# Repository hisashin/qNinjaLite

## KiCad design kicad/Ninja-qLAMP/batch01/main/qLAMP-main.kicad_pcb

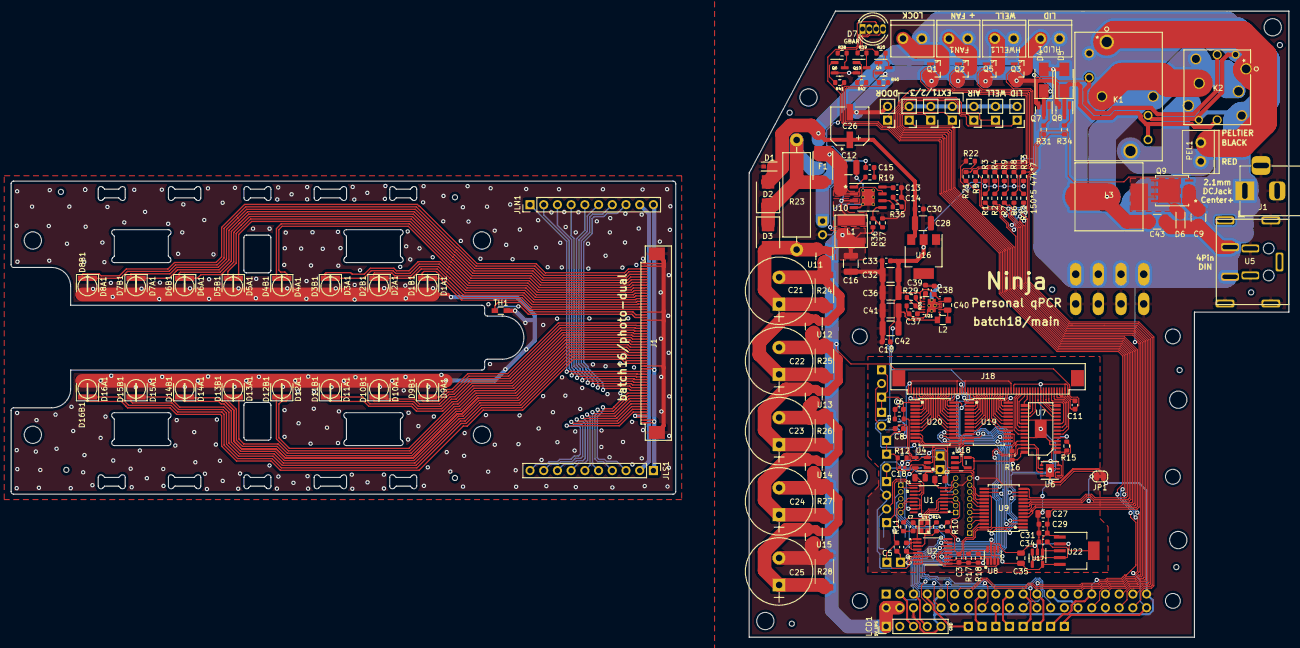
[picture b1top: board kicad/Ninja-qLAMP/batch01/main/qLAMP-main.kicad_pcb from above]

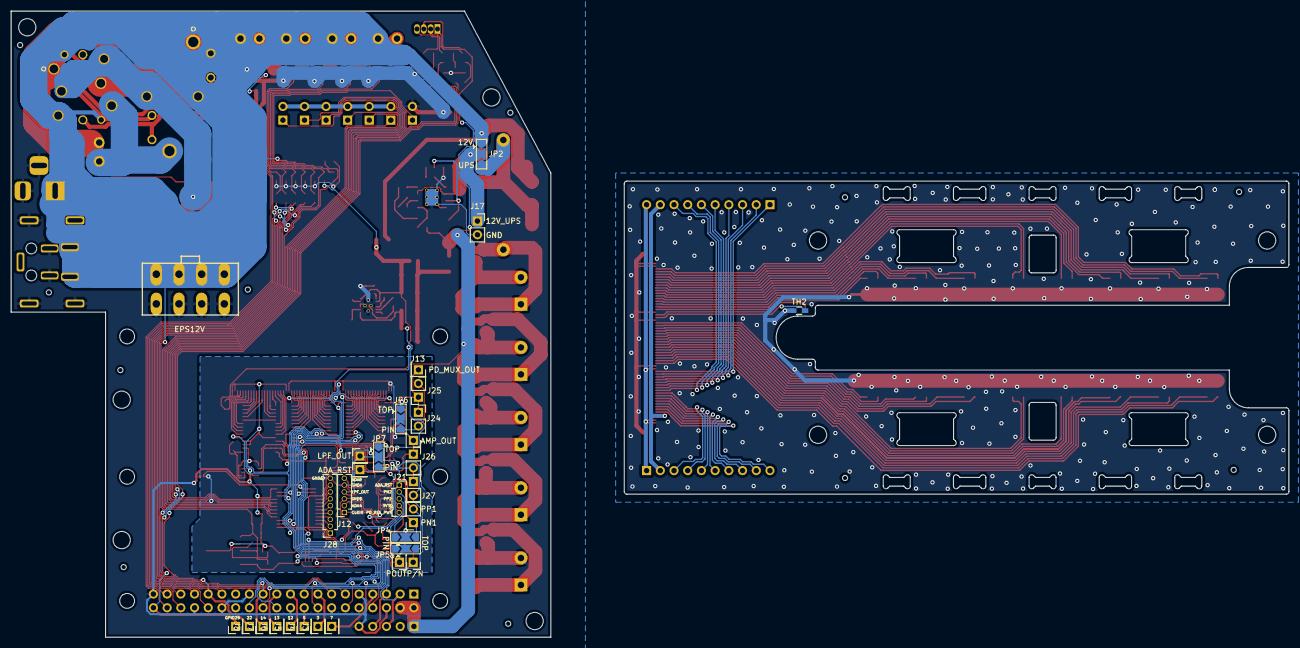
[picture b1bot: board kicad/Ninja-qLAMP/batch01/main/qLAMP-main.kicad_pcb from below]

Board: 2 copper layers, 100.0 x 116.0 mm, 210 parts (30 on the bottom side), 170 nets.

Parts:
C1, C2, C27, C35: 4.7uF; C_0805_2012Metric
C3, C4, C5, C7, C8, C10, C11, C13, C29, C30, C33: 0.1uF; C_0603_1608Metric
C6: DNP(<1pF); C_0603_1608Metric
C9, C12, C16, C28, C32, C36, C41, C42, C43: 22uF; C_1210_3225Metric
C14, C15, C31: 0.01uF; C_0603_1608Metric
C18: 330pF; C_0402_1005Metric
C21, C22, C23, C24, C25: 10F2.7V; CP_Radial_D12.5mm_P5.00mm
C26: 100uF; 35TZV100M6.3X8
C34: 100pF; C_0603_1608Metric
C37, C38, C39: 1uF; C_0603_1608Metric
C40: 10uF; C_0805_2012Metric
D1, D6: D_Schottky; MSS1P3L-M3&slash_89A
D1A1, D1B1, D2A1, D2B1, D3A1, D3B1, D4A1, D4B1, D5A1, D5B1, D6A1, D6B1, D7A1, D7B1, D8A1, D8B1, D9A1, D9B1, D10A1, D10B1, D11A1, D11B1, D12A1, D12B1, D13A1, D13B1, D14A1, D14B1, D15A1, D15B1, D16A1, D16B1: D_Photo; D_1206
D2, D3: D; D_SMB
D4, D5: DIODE; D_SMA
D7: LED_GBAR; LED_D5.0mm-4_RGB
F1: Fuse; R_2512
FAN1: Screw_Terminal_01x02; TB_SeeedOPL_320110028
HLID1: Screw_Terminal_01x02; TB_SeeedOPL_320110028
HWELL1: Screw_Terminal_01x02; TB_SeeedOPL_320110028
J1: Barrel_Jack_Switch; BarrelJack_Horizontal
J1#2, J18: Conn_01x60_Male; FFC_60_Ali_HUISHUNFA
J2: Raspberry_Pi_3A_Plus_wpi; Raspberry_Pi_3A+_3B+_4B_Zero_FaceDown_HDMI-R-NOSILK
J3, J4, J5, J6, J7, J8, J9, J11, J20, J23: Conn_01x01_Male; PinHeader_1x01_P2.54mm_Vertical
J12: Conn_01x06_Male; PinSocket_1x06_P1.27mm_Vertical
J13, J14, J15, J16: Conn_01x01_Male; PinSocket_1x01_P2.54mm_Vertical
J17, J22, J24, J25, J26, J27: Conn_01x02_Male; PinSocket_1x02_P2.54mm_Vertical
J19: Conn_01x08_Male; ATX8
J21: Conn_01x05_Male; PinSocket_1x05_P1.27mm_Vertical
J28: Conn_01x09_Male; PinSocket_1x09_P1.27mm_Vertical
JLN1: Conn_01x10_Male; Pin_Header_Straight_1x10_Pitch2.54mm
JLS1: Conn_01x10_Male; Pin_Header_Straight_1x10_Pitch2.54mm
JP1: SolderJumper_2_Bridged; SolderJumper-2_P1.3mm_Bridged_RoundedPad1.0x1.5mm
JP2, JP4, JP5, JP6, JP7: Jumper_3_Open; SolderJumper-3_P2.0mm_Open_TrianglePad1.0x1.5mm
K1: EP2-3L3SAb
K2: EX2-2U1S
L1: 10uH; VLS6045EX-3R3N
L2: 2.2uH; C_0805
L3: SRP1265C-220M; SRP1265C
LCD1: RPI_LCD_TOUCH_7INCH; PinHeader_1x05_P2.54mm_Vertical
LOCK1: Conn_01x02_Male; TB_SeeedOPL_320110028
PEL1: Screw_Terminal_01x02; TB_SeeedOPL_320110028
Q1, Q2, Q3, Q5: Q_NMOS_GSD; SOT95P240X112-3N
Q4, Q6, Q7, Q8, Q10: Q_NPN_BCE; SOT-23
Q9: SIRA88BDP-T1-GE3; PowerPAK_SO-8_Long
R1, R2, R6, R7, R19, R32: 150; R_0603_1608Metric
R3, R4, R5, R8, R9, R16, R21, R33, R36: 47k; R_0603_1608Metric
R10, R11, R12, R14, R22, R31, R34, R35, R37, R40, R41, R42: 10k; R_0603_1608Metric
R13: 10M; R_0603_1608Metric
R15: 180; R_0603_1608Metric
R17: 10k_HP; R_0603_1608Metric
R18: 47k_HP; R_0603_1608Metric
R20, R38, R39: ?; R_0603_1608Metric
R23: 8.2Ω 3W; R_Axial_DIN0516_L15.5mm_D5.0mm_P20.32mm_Horizontal
R24, R25, R26, R27, R28: 1k2W; R_2512_6332Metric
R29: 39k; R_0603_1608Metric
R30: 150k; R_0603_1608Metric
SW1: SW_Reed; PinHeader_1x02_P2.54mm_Vertical
TAIR1: Conn_01x02_Male; PinHeader_1x02_P2.54mm_Vertical
TEXT1, TEXT2, TEXT3: Conn_01x02_Male; PinHeader_1x02_P2.54mm_Vertical
TH1, TH2: Thermistor; R_0603_HandSoldering
TLID1: Conn_01x02_Male; PinHeader_1x02_P2.54mm_Vertical
TWELL1: Conn_01x02_Male; PinHeader_1x02_P2.54mm_Vertical
U1: ADA2200ARUZ
U2: ADS1219IPWR; ADS122C04IPWR
U3: COM1305-0.032768-EXT-T-TR; ASDK-32.768KHZ-LRT
U4: LMP7717MF_NOPB; SOT-23-5
U5: DIN4_PWR; DN4_PWR
U6: MCP4551T-502E/MS; MCP4551T-104E&slash_MF
U7: PCA9955B
U8: TS12A12511DCNR; SOT-23-8
U9, U19, U20: CD74HC4067M96; SSOP-24_5.3x8.2mm_P0.65mm
U10: BD9329AEFJ-E2; HSOP-8-1EP_3.9x4.9mm_P1.27mm_EP2.41x3.1mm_ThermalVias
U11, U12, U13, U14, U15: TL431DBZ; SOT-23
U16: CJT1117-3.3; SOT-223
U17: MCP1755T-3302E/OT; SOT-23-5
U18: SN74LVC1GU04DCKR; SN74LVC1GU04DBVR
U21: TPS63710DRRR
U22: MCP1755T-3302E/DC; SOT-223-6

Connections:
3V3A: C3.1, C35.1, R17.1, R18.1, U2.9 (REFP), U2.12 (AVDD), U17.5 (VOUT), U22.5 (VOUT)
3V3D: C3.2, C7.1, C10.1, C32.1, C33.1, C36.1, C38.1, J21.4, R5.1, R10.2, R11.2, R14.2, R16.2, U1.12 (VDD), U1.14 (SDIO/SDA), U1.15 (SCLK/SCL), U2.3 (RESET_N), U2.13 (DVDD), U3.4 (3V3), U4.5 (V+), U6.1 (HVC/A0), U6.5 (P0A), U6.8 (VDD), U7.2 (AD0), U7.28 (VDD), U8.4 (V+), U9.15 (*E), U9.24 (VCC), U16.2 (OUTPUT), U18.5, U19.24 (VCC), U20.24 (VCC), U21.2 (EN), U21.12 (VIN)
5V_UPS: C11.1, C16.2, D7.3 (A), J2.2 (5V), J2.4 (5V), J18.3, J18.4, L1.1, LCD1.1 (5V), R36.1
12V: C9.1, C26.1, C27.1, C28.1, C29.1, C30.1, C31.1, C43.1, D1.1 (K), D2.2 (A), D4.2 (A), D5.2 (A), D6.1 (K), FAN1.1, HLID1.1, HWELL1.1, J1.1, J19.5, J19.6, J19.7, J19.8, JP2.1 (A), K1.2, K1.4, K1.6, K2.2, K2.5, K2.7, K2.9, LOCK1.1, R21.1, U5.1 (VIN1), U5.2 (VIN2), U16.3 (INPUT), U17.1 (VIN), U17.3 (SHDN), U22.1 (VIN), U22.3 (SHDN)
12V_UPS: C12.2, F1.1, J17.1, JP2.2 (C), U10.2 (IN), U10.7 (EN)
-1V: C41.1, C42.1, L2.2, U4.2 (V-), U18.3, U19.12 (GND), U20.12 (GND), U21.7 (VOUT)
/3V3/PWRGD: C34.1, U17.4 (PWRGD), U22.4 (PWRGD)
/5V_UPS/5V_SW: C15.2, L1.2, U10.3 (SW)
/FAN: J2.29 (GPIO21), R2.2
/GPIO3: J2.15 (GPIO3), J3.1
/GPIO5: J2.18 (GPIO5), J4.1
/GPIO7: J2.7 (GPIO7), J11.1
/GPIO12: J2.19 (GPIO12/MOSI), J5.1
/GPIO13: J2.21 (GPIO13/MISO), J6.1
/GPIO14: J2.23 (GPIO14/SCLK), J7.1, R40.2
/GPIO22: J2.31 (GPIO22), J8.1, R41.2
/GPIO29: J2.40 (GPIO29), J9.1, R42.2
/LID_HEATER: J2.13 (GPIO2), R6.2
/Photo/ADA4: J12.2, R11.1, U1.4 (*BOOT)
/Photo/ADA8: C2.1, J12.6, U1.8 (VOCM)
/Photo/ADA_RST: C1.1, J20.1, J21.1, R10.1, U1.9 (*RST)
/Photo/AMP_OUT: C8.1, J16.1, J26.1, JP6.2 (C), R12.2, U4.1 (OUT)
/Photo/LPF_OUT: J12.4, J23.1, JP7.2 (C), U1.6 (INP)
/Photo/PHOTO_OUT_N: C5.1, J14.1, JP4.2 (C), U2.7 (AIN2)
/Photo/PHOTO_OUT_P: C5.2, J15.1, JP5.2 (C), U2.6 (AIN3)
/Photo/PN1: J22.1, JP4.3 (B), U1.10 (OUTN)
/Photo/PN2: J21.2, JP4.1 (A)
/Photo/PP1: J22.2, JP5.3 (B), U1.11 (OUTP)
/Photo/PP2: J21.3, JP5.1 (A)
/PhotoLED/LED_IREF: R15.2, U6.6 (P0W)
/PhotoMUX/MUX_SELECT_INV: U18.4, U19.15 (*E)
/PhotoMUX/N_PD_OUT1: J18.43, U20.23 (I8)
/PhotoMUX/N_PD_OUT2: J18.44, U20.22 (I9)
/PhotoMUX/N_PD_OUT3: J18.45, U20.21 (I10)
/PhotoMUX/N_PD_OUT4: J18.46, U20.20 (I11)
/PhotoMUX/N_PD_OUT5: J18.47, U20.19 (I12)
/PhotoMUX/N_PD_OUT6: J18.48, U20.18 (I13)
/PhotoMUX/N_PD_OUT7: J18.49, U20.17 (I14)
/PhotoMUX/N_PD_OUT8: J18.50, U20.16 (I15)
/PhotoMUX/N_PD_OUT9: J18.51, U20.9 (I0)
/PhotoMUX/N_PD_OUT10: J18.52, U20.8 (I1)
/PhotoMUX/N_PD_OUT11: J18.53, U20.7 (I2)
/PhotoMUX/N_PD_OUT12: J18.54, U20.6 (I3)
/PhotoMUX/N_PD_OUT13: J18.55, U20.5 (I4)
/PhotoMUX/N_PD_OUT14: J18.56, U20.4 (I5)
/PhotoMUX/N_PD_OUT15: J18.57, U20.3 (I6)
/PhotoMUX/N_PD_OUT16: J18.58, U20.2 (I7)
/PhotoMUX/S_PD_OUT1: J18.38, U19.2 (I7)
/PhotoMUX/S_PD_OUT2: J18.37, U19.3 (I6)
/PhotoMUX/S_PD_OUT3: J18.36, U19.4 (I5)
/PhotoMUX/S_PD_OUT4: J18.35, U19.5 (I4)
/PhotoMUX/S_PD_OUT5: J18.34, U19.6 (I3)
/PhotoMUX/S_PD_OUT6: J18.33, U19.7 (I2)
/PhotoMUX/S_PD_OUT7: J18.32, U19.8 (I1)
/PhotoMUX/S_PD_OUT8: J18.31, U19.9 (I0)
/PhotoMUX/S_PD_OUT9: J18.30, U19.16 (I15)
/PhotoMUX/S_PD_OUT10: J18.29, U19.17 (I14)
/PhotoMUX/S_PD_OUT11: J18.28, U19.18 (I13)
/PhotoMUX/S_PD_OUT12: J18.27, U19.19 (I12)
/PhotoMUX/S_PD_OUT13: J18.26, U19.20 (I11)
/PhotoMUX/S_PD_OUT14: J18.25, U19.21 (I10)
/PhotoMUX/S_PD_OUT15: J18.24, U19.22 (I9)
/PhotoMUX/S_PD_OUT16: J18.23, U19.23 (I8)
/SheetPeltier/PEL1: D4.1 (K), K1.3, K2.3, Q7.3 (C)
/SheetPeltier/PEL3: D5.1 (K), K1.7, K2.8, Q8.3 (C)
/SheetPeltier/PEL_BLK: K1.1, K2.1, PEL1.2
/SheetPeltier/PEL_RED: K1.8, K2.6, PEL1.1
/SheetPeltier/REG_D: D6.2 (A), L3.1, Q9.5 (D), Q9.6 (D), Q9.7 (D), Q9.8 (D)
/WELL_HEATER: J2.33 (GPIO23/PWM1), R7.2
ADC_DRDY: J2.24 (GPIO10/CE0), U2.14 (DRDY_N)
CLKIN: J12.1, U1.1 (CLKIN), U3.3 (OUT)
DLOCK: J2.37 (GPIO25), R1.2
DOPEN: J2.35 (GPIO24), R5.2, SW1.1
GNDA: C2.2, C4.1, C8.2, C18.2, D1A1.2, D1B1.2, D2A1.2, D2B1.2, D3A1.2, D3B1.2, D4A1.2, D4B1.2, D5A1.2, D5B1.2, D6A1.2, D6B1.2, D7A1.2, D7B1.2, D8A1.2, D8B1.2, D9A1.2, D9B1.2, D10A1.2, D10B1.2, D11A1.2, D11B1.2, D12A1.2, D12B1.2, D13A1.2, D13B1.2, D14A1.2, D14B1.2, D15A1.2, D15B1.2, D16A1.2, D16B1.2, J1#2.22, J1#2.39, J1#2.42, J1#2.59, J1#2.60, J1#2.G1, J1#2.G2, J12.5, J18.22, J18.39, J18.42, J18.59, J18.60, J27.2, J28.9, JP1.2 (B), TAIR1.2, TEXT1.2, TEXT2.2, TEXT3.2, TH1.2, TH2.2, TLID1.2, TWELL1.2, U1.7 (INN), U2.5 (AVSS), U2.8 (REFN), U2.11 (AIN0), U4.3 (IN+)
GNDD: C1.2, C4.2, C7.2, C9.2, C10.2, C11.2, C12.1, C13.1, C14.1, C16.1, C25.2, C26.2, C27.2, C28.2, C29.2, C30.2, C31.2, C32.2, C33.2, C34.2, C35.2, C36.2, C37.2, C38.2, C39.2, C41.2, C42.2, D1.2 (A), J1.2, J1.3, J2.6 (GND), J2.9 (GND), J2.14 (GND), J2.20 (GND), J2.25 (GND), J2.30 (GND), J2.34 (GND), J2.39 (GND), J12.3, J17.2, J18.1, J18.2, J18.21, J19.1, J19.2, J19.3, J19.4, JP1.1 (A), LCD1.5 (GND), Q1.2 (S), Q2.2 (S), Q3.2 (S), Q4.2 (E), Q5.2 (S), Q6.2 (E), Q7.2 (E), Q8.2 (E), Q9.1 (S), Q9.2 (S), Q9.3 (S), Q10.2 (E), R3.1, R4.1, R8.1, R9.1, R22.2, R28.1, R30.2, R33.2, R37.2, SW1.2, U1.5 (GND), U2.1 (A0), U2.2 (A1), U2.4 (DGND), U3.2 (GND), U5.3 (GND), U5.4 (GND), U5.6 (CASE), U5.7 (CASE), U5.9 (CASE), U6.4 (VSS), U6.7 (P0B), U6.9 (EP), U7.3 (AD1), U7.4 (AD2), U7.10 (VSS), U7.19 (VSS), U7.24 (VSS), U7.29 (VSS), U8.3 (GND), U8.7 (V-), U9.12 (GND), U10.4 (GND), U10.9 (EP), U15.3 (A), U16.1 (ADJ/GND), U17.2 (GND), U21.9 (GND), U21.10 (GND), U21.13 (PAD), U22.2 (GND), U22.6 (EP)
I2C_SCL: J2.5 (GPIO9/SCL1), LCD1.4 (SCL), U2.16 (SCL), U6.2 (SCL), U7.26 (SCL)
I2C_SDA: J2.3 (GPIO8/SDA1), LCD1.3 (SDA), U2.15 (SDA), U6.3 (SDA), U7.27 (SDA)
MUX_S0: J2.16 (GPIO4), U9.10 (S0), U19.10 (S0), U20.10 (S0)
MUX_S1: J2.12 (GPIO1/PWM0), U9.11 (S1), U19.11 (S1), U20.11 (S1)
MUX_S2: J2.8 (GPIO15/TXD), U9.14 (S2), U19.14 (S2), U20.14 (S2)
MUX_S3: J2.10 (GPIO16/RXD), U9.13 (S3), U19.13 (S3), U20.13 (S3)
MUX_SELECT: J2.22 (GPIO6), U18.2, U20.15 (*E)
N_LED_OUT1: J18.20, U7.23 (LED15)
N_LED_OUT2: J18.19, U7.22 (LED14)
N_LED_OUT3: J18.18, U7.21 (LED13)
N_LED_OUT4: J18.17, U7.20 (LED12)
N_LED_OUT5: J18.16, U7.15 (LED8)
N_LED_OUT6: J18.15, U7.16 (LED9)
N_LED_OUT7: J18.14, U7.17 (LED10)
N_LED_OUT8: J18.13, U7.18 (LED11)
unnamed: C6.1, JP6.1 (A), R13.2
unnamed: C13.2, U10.8 (SS)
unnamed: C14.2, R35.2
unnamed: C15.1, R19.2
unnamed: C18.1, JP7.1 (A), R12.1
unnamed: C21.1, D3.2 (A), R23.1, R24.2, U11.1 (K), U11.2 (REF)
unnamed: C21.2, C22.1, R24.1, R25.2, U11.3 (A), U12.1 (K), U12.2 (REF)
unnamed: C22.2, C23.1, R25.1, R26.2, U12.3 (A), U13.1 (K), U13.2 (REF)
unnamed: C23.2, C24.1, R26.1, R27.2, U13.3 (A), U14.1 (K), U14.2 (REF)
unnamed: C24.2, C25.1, R27.1, R28.2, U14.3 (A), U15.1 (K), U15.2 (REF)
unnamed: C37.1, U21.6 (CAP)
unnamed: C39.1, U21.1 (VAUX)
unnamed: C40.1, U21.11 (CP)
unnamed: C40.2, L2.1, U21.8 (SW)
unnamed: D2.1 (K), D3.1 (K), F1.2, JP2.3 (B), R23.2
unnamed: D7.1 (GK), R38.1
unnamed: D7.2 (BK), R39.1
unnamed: D7.4 (RK), R20.1
unnamed: FAN1.2, Q2.3 (D)
unnamed: HLID1.2, Q3.3 (D)
unnamed: HWELL1.2, Q5.3 (D)
unnamed: J24.2, J25.2, JP6.3 (B)
unnamed: J26.2, J27.1, JP7.3 (B)
unnamed: LOCK1.2, Q1.3 (D)
unnamed: Q1.1 (G), R1.1, R3.2
unnamed: Q2.1 (G), R2.1, R4.2
unnamed: Q3.1 (G), R6.1, R8.2
unnamed: Q4.1 (B), R40.1
unnamed: Q4.3 (C), R20.2
unnamed: Q5.1 (G), R7.1, R9.2
unnamed: Q6.1 (B), R41.1
unnamed: Q6.3 (C), R38.2
unnamed: Q7.1 (B), R31.1
unnamed: Q8.1 (B), R34.2
unnamed: Q9.4 (G), R32.1, R33.1
unnamed: Q10.1 (B), R42.1
unnamed: Q10.3 (C), R39.2
unnamed: R14.1, U3.1 (EN)
unnamed: R15.1, U7.1 (REXT)
unnamed: R16.1, U7.25 (RESET)
unnamed: R17.2, U8.8 (NO)
unnamed: R18.2, U8.2 (NC)
unnamed: R19.1, U10.1 (BST)
unnamed: R29.1, U21.4 (VREF)
unnamed: R29.2, R30.1, U21.5 (FB)
unnamed: R35.1, U10.6 (COMP)
unnamed: R36.2, R37.1, U10.5 (FB)
PD_MUX_OUT: C6.2, J13.1, J24.1, J25.1, R13.1, U4.4 (IN-), U19.1 (COMMONINPUT/OUTPUT), U20.1 (COMMONINPUT/OUTPUT)
PD_REF_PWM: J21.5, U1.13 (RCLK/SDO), U7.5 (OE)
PD_TH1: J18.40, U9.3 (I6)
PD_TH2: J18.41, U9.2 (I7)
PEL_PWM: J2.32 (GPIO26/PWM0), R32.2
PEL_SWA: J2.36 (GPIO27), R31.2
PEL_SWB: J2.38 (GPIO28), R34.1
REG_OUT: C43.2, K1.5, K2.4, K2.10, L3.2
S_LED_OUT1: J18.12, U7.11 (LED4)
S_LED_OUT2: J18.11, U7.12 (LED5)
S_LED_OUT3: J18.10, U7.13 (LED6)
S_LED_OUT4: J18.9, U7.14 (LED7)
S_LED_OUT5: J18.8, U7.9 (LED3)
S_LED_OUT6: J18.7, U7.8 (LED2)
S_LED_OUT7: J18.6, U7.7 (LED1)
S_LED_OUT8: J18.5, U7.6 (LED0)
THERM_AIR: TAIR1.1, U9.8 (I1)
THERM_EXT1: TEXT1.1, U9.6 (I3)
THERM_EXT2: TEXT2.1, U9.5 (I4)
THERM_EXT3: TEXT3.1, U9.4 (I5)
THERM_EXT4: J28.1, U9.23 (I8)
THERM_EXT5: J28.2, U9.22 (I9)
THERM_EXT6: J28.3, U9.21 (I10)
THERM_EXT7: J28.4, U9.20 (I11)
THERM_EXT8: J28.5, U9.19 (I12)
THERM_EXT9: J28.6, U9.18 (I13)
THERM_EXT10: J28.7, U9.17 (I14)
THERM_EXT11: J28.8, U9.16 (I15)
THERM_LID: TLID1.1, U9.7 (I2)
THERM_MUX_OUT: U2.10 (AIN1), U8.1 (COM), U9.1 (COMMONINPUT/OUTPUT)
THERM_R_SWITCH: J2.26 (GPIO11/CE1), U8.6 (IN)
THERM_WELL: TWELL1.1, U9.9 (I0)
VIN_SENSE: J2.11 (GPIO0), R21.2, R22.1

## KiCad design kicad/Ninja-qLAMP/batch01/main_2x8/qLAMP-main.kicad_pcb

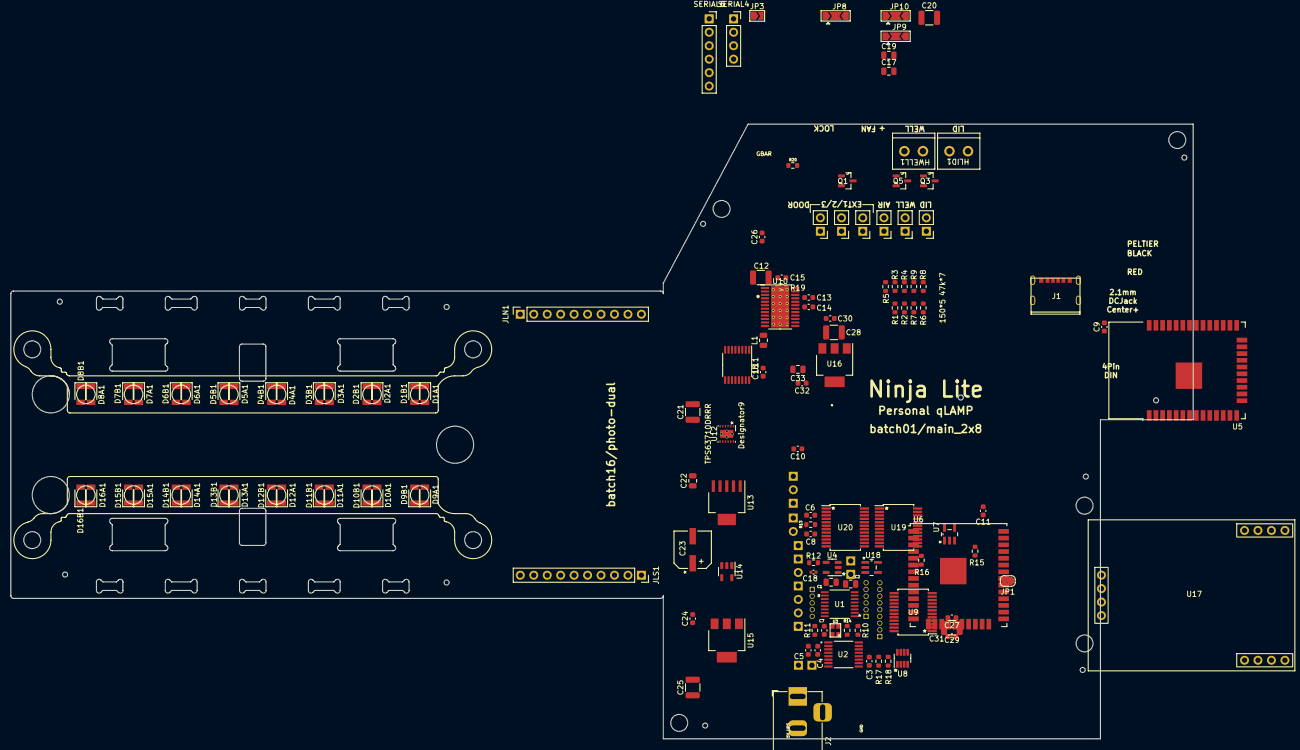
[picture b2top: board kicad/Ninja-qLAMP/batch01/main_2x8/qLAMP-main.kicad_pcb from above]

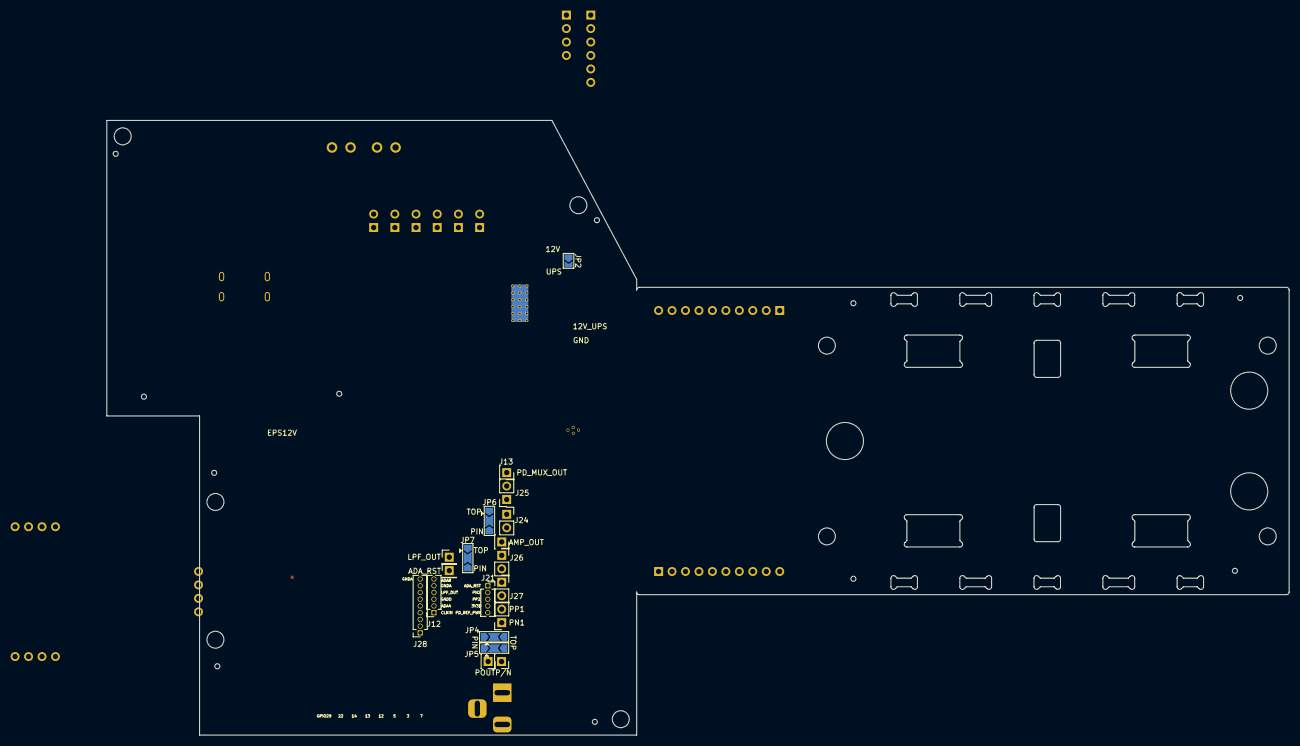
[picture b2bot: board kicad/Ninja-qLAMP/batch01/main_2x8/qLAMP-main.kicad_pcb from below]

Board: 2 copper layers, 223.1 x 116.0 mm, 147 parts (19 on the bottom side), 126 nets, no tracks yet.

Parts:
C1, C2, C22, C33: 4.7uF; C_0805_2012Metric
C3, C4, C5, C7, C8, C9, C10, C11, C24, C27, C31, C32: 0.1uF; C_0603_1608Metric
C6: DNP(<1pF); C_0603_1608Metric
C12, C20, C21, C25, C28, C29: 22uF; C_1210_3225Metric
C13: 1uF(<=20V); C_0603_1608Metric
C14, C15, C16: 1uF; C_0603_1608Metric
C17: 10uF(<=20V); C_0805_2012Metric
C18: 330pF; C_0402_1005Metric
C19: 10uF; C_0805_2012Metric
C23: 100uF; 35TZV100M6.3X8
C26: 0.01uF; C_0603_1608Metric
C30: 100pF; C_0603_1608Metric
D1A1, D1B1, D2A1, D2B1, D3A1, D3B1, D4A1, D4B1, D5A1, D5B1, D6A1, D6B1, D7A1, D7B1, D8A1, D8B1, D9A1, D9B1, D10A1, D10B1, D11A1, D11B1, D12A1, D12B1, D13A1, D13B1, D14A1, D14B1, D15A1, D15B1, D16A1, D16B1: D_Photo; D_1206
HLID1: Screw_Terminal_01x02; TB_SeeedOPL_320110028
HWELL1: Screw_Terminal_01x02; TB_SeeedOPL_320110028
J1: ALI_USB
J2: Barrel_Jack_Switch; BarrelJack_Horizontal
J12: Conn_01x06_Male; PinSocket_1x06_P1.27mm_Vertical
J13, J14, J15, J16: Conn_01x01_Male; PinSocket_1x01_P2.54mm_Vertical
J20, J23: Conn_01x01_Male; PinHeader_1x01_P2.54mm_Vertical
J21: Conn_01x05_Male; PinSocket_1x05_P1.27mm_Vertical
J22, J24, J25, J26, J27: Conn_01x02_Male; PinSocket_1x02_P2.54mm_Vertical
J28: Conn_01x09_Male; PinSocket_1x09_P1.27mm_Vertical
JLN1: Conn_01x10_Male; PinSocket_1x10_P2.54mm_Vertical
JLS1: Conn_01x10_Male; PinSocket_1x10_P2.54mm_Vertical
JP1: SolderJumper_2_Bridged; SolderJumper-2_P1.3mm_Bridged_RoundedPad1.0x1.5mm
JP2, JP3: Jumper_2_Bridged; SolderJumper-2_P1.3mm_Open_TrianglePad1.0x1.5mm
JP4, JP5, JP6, JP7, JP8, JP9, JP10: Jumper_3_Open; SolderJumper-3_P2.0mm_Open_TrianglePad1.0x1.5mm
L1: 2.2uH; C_0805_2012Metric
Q1, Q3, Q5: Q_NMOS_GSD; SOT95P240X112-3N
R1, R10, R11, R12, R14, R20: 10k; R_0603_1608Metric
R2: 0; R_0603_1608Metric
R3, R4: 5.1k; R_0603_1608Metric
R5: 39k; R_0603_1608Metric
R6, R7: 150; R_0603_1608Metric
R8, R9: 47k; R_0603_1608Metric
R13: 10M; R_0603_1608Metric
R15: 150k; R_0603_1608Metric
R16, R19: 100k; R_0603_1608Metric
R17: 10k_HP; R_0603_1608Metric
R18: 47k_HP; R_0603_1608Metric
SERIAL4: Conn_01x04_Male; PinSocket_1x04_P2.54mm_Vertical
SERIAL6: Conn_01x06_Male; PinSocket_1x06_P2.54mm_Vertical
TAIR1: Conn_01x02_Male; PinHeader_1x02_P2.54mm_Vertical
TEXT1, TEXT2, TEXT3: Conn_01x02_Male; PinHeader_1x02_P2.54mm_Vertical
TLID1: Conn_01x02_Male; PinHeader_1x02_P2.54mm_Vertical
TWELL1: Conn_01x02_Male; PinHeader_1x02_P2.54mm_Vertical
U1: ADA2200ARUZ
U2: ADS1219IPWR; ADS122C04IPWR
U3: COM1305-0.032768-EXT-T-TR; ASDK-32.768KHZ-LRT
U4: LMP7717MF_NOPB; SOT-23-5
U5: ESP32-WROOM-32
U6: ESP32-WROOM-32U
U7, U18: SN74LVC1GU04DCKR; SN74LVC1GU04DBVR
U8: TS12A12511DCNR; SOT-23-8
U9, U19, U20: CD74HC4067M96; SSOP-24_5.3x8.2mm_P0.65mm
U10: TLC5929; HTSSOP-24-1EP_4.4x7.8mm_P0.65mm_EP3.4x7.8mm_Mask2.4x4.68mm_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
U11: IP2721; TSSOP-16_4.4x5mm_P0.65mm
U12: TPS63710DRRR
U13: MCP1755T-3302E_DC; SOT-223-6
U14: MCP1755T-3302E_OT; SOT-23-5
U15: CJT1117-3.3; SOT-223
U16: CJT1117-5.0; SOT-223
U17: LITE_LCD

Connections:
3V3A: C3.1, C33.1, R17.1, R18.1, U2.9 (REFP), U2.12 (AVDD), U13.5 (VOUT), U14.5 (VOUT)
3V3D: C3.2, C7.1, C10.1, C12.1, C15.1, C28.1, C31.1, J21.4, JP2.2 (B), JP3.2 (B), R1.1, R10.2, R11.2, R14.2, U1.12 (VDD), U1.14 (SDIO/SDA), U1.15 (SCLK/SCL), U2.3 (RESET_N), U2.13 (DVDD), U3.4 (3V3), U4.5 (V+), U5.2 (VDD), U6.2 (VDD), U7.5, U8.4 (V+), U9.15 (*E), U9.24 (VCC), U10.24 (VCC), U12.2 (EN), U12.12 (VIN), U15.2 (OUTPUT), U17.1 (VCC), U18.5, U19.24 (VCC), U20.24 (VCC)
5V: C11.1, C29.1, C32.1, JLN1.9, JLS1.2, U16.2 (OUTPUT)
12V: C17.1, C22.1, C23.1, C24.1, C25.1, C26.1, C27.1, HLID1.1, HWELL1.1, J2.1, Q1.2 (S), R16.2, R19.1, U11.16 (VBUS), U13.1 (VIN), U13.3 (SHDN), U14.1 (VIN), U14.3 (SHDN), U15.3 (INPUT), U16.3 (INPUT)
-1V: C20.1, C21.1, L1.2, U4.2 (V-), U12.7 (VOUT), U18.3, U19.12 (GND), U20.12 (GND)
/EN: C9.1, R1.2, U5.3 (EN), U6.3 (EN)
/Photo/ADA4: J12.2, R11.1, U1.4 (*BOOT)
/Photo/ADA8: C2.1, J12.6, U1.8 (VOCM)
/Photo/ADA_RST: C1.1, J20.1, J21.1, R10.1, U1.9 (*RST)
/Photo/AMP_OUT: C8.1, J16.1, J26.1, JP6.2 (C), R12.2, U4.1 (OUT)
/Photo/LPF_OUT: J12.4, J23.1, JP7.2 (C), U1.6 (INP)
/Photo/PHOTO_OUT_N: C5.1, J14.1, JP4.2 (C), U2.7 (AIN2)
/Photo/PHOTO_OUT_P: C5.2, J15.1, JP5.2 (C), U2.6 (AIN3)
/Photo/PN1: J22.1, JP4.3 (B), U1.10 (OUTN)
/Photo/PN2: J21.2, JP4.1 (A)
/Photo/PP1: J22.2, JP5.3 (B), U1.11 (OUTP)
/Photo/PP2: J21.3, JP5.1 (A)
/PhotoLED/LED_BLANK: JP8.2 (C), U10.21 (BLANK)
/PhotoLED/N_LED_OUT1: JLN1.8, U10.20 (OUT15)
/PhotoLED/N_LED_OUT2: JLN1.7, U10.19 (OUT14)
/PhotoLED/N_LED_OUT3: JLN1.6, U10.18 (OUT13)
/PhotoLED/N_LED_OUT4: JLN1.5, U10.17 (OUT12)
/PhotoLED/N_LED_OUT5: JLN1.4, U10.13 (OUT8)
/PhotoLED/N_LED_OUT6: JLN1.3, U10.14 (OUT9)
/PhotoLED/N_LED_OUT7: JLN1.2, U10.15 (OUT10)
/PhotoLED/N_LED_OUT8: JLN1.1, U10.16 (OUT11)
/PhotoLED/S_LED_OUT1: JLS1.3, U10.9 (OUT4)
/PhotoLED/S_LED_OUT2: JLS1.4, U10.10 (OUT5)
/PhotoLED/S_LED_OUT3: JLS1.5, U10.11 (OUT6)
/PhotoLED/S_LED_OUT4: JLS1.6, U10.12 (OUT7)
/PhotoLED/S_LED_OUT5: JLS1.7, U10.8 (OUT3)
/PhotoLED/S_LED_OUT6: JLS1.8, U10.7 (OUT2)
/PhotoLED/S_LED_OUT7: JLS1.9, U10.6 (OUT1)
/PhotoLED/S_LED_OUT8: JLS1.10, U10.5 (OUT0)
/PhotoMUX/MUX_SELECT_INV: U18.4, U20.15 (*E)
/Power/PWRGD: C30.1, U13.4 (PWRGD), U14.4 (PWRGD)
/Power/SEL: JP9.2 (C), U11.11 (SEL)
/Power/SELP: JP10.2 (C), U11.6 (SELP)
/RXD: SERIAL4.2, SERIAL6.3
/TXD: SERIAL4.3, SERIAL6.2
CLKIN: J12.1, U1.1 (CLKIN), U3.3 (OUT)
GNDA: C2.2, C4.1, C8.2, C18.2, D1A1.2 (A), D1B1.2 (A), D2A1.2 (A), D2B1.2 (A), D3A1.2 (A), D3B1.2 (A), D4A1.2 (A), D4B1.2 (A), D5A1.2 (A), D5B1.2 (A), D6A1.2 (A), D6B1.2 (A), D7A1.2 (A), D7B1.2 (A), D8A1.2 (A), D8B1.2 (A), D9A1.2 (A), D9B1.2 (A), D10A1.2 (A), D10B1.2 (A), D11A1.2 (A), D11B1.2 (A), D12A1.2 (A), D12B1.2 (A), D13A1.2 (A), D13B1.2 (A), D14A1.2 (A), D14B1.2 (A), D15A1.2 (A), D15B1.2 (A), D16A1.2 (A), D16B1.2 (A), J12.5, J27.2, J28.9, JP1.2 (B), TAIR1.2, TEXT1.2, TEXT2.2, TEXT3.2, TLID1.2, TWELL1.2, U1.7 (INN), U2.5 (AVSS), U2.8 (REFN), U2.11 (AIN0), U4.3 (IN+)
GNDD: C1.2, C4.2, C7.2, C9.2, C10.2, C11.2, C12.2, C13.2, C14.2, C15.2, C16.2, C17.2, C20.2, C21.2, C22.2, C23.2, C24.2, C25.2, C26.2, C27.2, C28.2, C29.2, C30.2, C31.2, C32.2, C33.2, J1.A12 (GND), J1.B12 (GND), J2.2, J2.3, J12.3, JLN1.10, JLS1.1, JP1.1 (A), JP9.3 (B), JP10.3 (B), Q3.2 (S), Q5.2 (S), R2.2, R3.1, R4.1, R8.1, R9.1, R15.2, R20.2, SERIAL4.4, SERIAL6.6, U1.5 (GND), U2.1 (A0), U2.2 (A1), U2.4 (DGND), U3.2 (GND), U5.1 (GND), U5.15 (GND), U5.38 (GND), U5.39 (GND), U6.1 (GND), U6.15 (GND), U6.38 (GND), U6.39 (GND), U7.3, U8.3 (GND), U8.7 (V-), U9.12 (GND), U10.1 (GND), U11.5 (GND), U12.9 (GND), U12.10 (GND), U12.13 (PAD), U13.2 (GND), U13.6 (EP), U14.2 (GND), U15.1 (ADJ/GND), U16.1 (ADJ/GND), U17.4 (GND), U17.8 (GND)
I2C_SCL: U2.16 (SCL), U17.2 (SCL)
I2C_SDA: U2.15 (SDA), U17.3 (SDA)
MUX_S0: U9.10 (S0), U19.10 (S0), U20.10 (S0)
MUX_S1: U9.11 (S1), U19.11 (S1), U20.11 (S1)
MUX_S2: U9.14 (S2), U19.14 (S2), U20.14 (S2)
MUX_S3: U9.13 (S3), U19.13 (S3), U20.13 (S3)
MUX_SELECT: U18.2, U19.15 (*E)
N_PD_OUT1: D1A1.1 (K), U20.23 (I8)
N_PD_OUT2: D1B1.1 (K), U20.22 (I9)
N_PD_OUT3: D2A1.1 (K), U20.21 (I10)
N_PD_OUT4: D2B1.1 (K), U20.20 (I11)
N_PD_OUT5: D3A1.1 (K), U20.19 (I12)
N_PD_OUT6: D3B1.1 (K), U20.18 (I13)
N_PD_OUT7: D4A1.1 (K), U20.17 (I14)
N_PD_OUT8: D4B1.1 (K), U20.16 (I15)
N_PD_OUT9: D5A1.1 (K), U20.9 (I0)
N_PD_OUT10: D5B1.1 (K), U20.8 (I1)
N_PD_OUT11: D6A1.1 (K), U20.7 (I2)
N_PD_OUT12: D6B1.1 (K), U20.6 (I3)
N_PD_OUT13: D7A1.1 (K), U20.5 (I4)
N_PD_OUT14: D7B1.1 (K), U20.4 (I5)
N_PD_OUT15: D8A1.1 (K), U20.3 (I6)
N_PD_OUT16: D8B1.1 (K), U20.2 (I7)
unnamed: C6.1, JP6.1 (A), R13.2
unnamed: C13.1, J1.A9 (VBUS), J1.B9 (VBUS), Q1.3 (D), U11.2 (VIN)
unnamed: C14.1, U12.6 (CAP)
unnamed: C16.1, U12.1 (VAUX)
unnamed: C18.1, JP7.1 (A), R12.1
unnamed: C19.1, U12.11 (CP)
unnamed: C19.2, L1.1, U12.8 (SW)
unnamed: HLID1.2, Q3.3 (D)
unnamed: HWELL1.2, Q5.3 (D)
unnamed: J1.A5 (CC1), R3.2, U11.13 (CC1)
unnamed: J1.B5 (CC2), R4.2, U11.12 (CC2)
unnamed: J24.2, J25.2, JP6.3 (B)
unnamed: J26.2, J27.1, JP7.3 (B)
unnamed: JP2.1 (A), SERIAL6.4
unnamed: JP3.1 (A), SERIAL4.1
unnamed: JP8.3 (B), U7.4
unnamed: JP9.1 (A), JP10.1 (A), R16.1
unnamed: Q1.1 (G), U11.1 (VBUSG)
unnamed: Q3.1 (G), R6.1, R8.2
unnamed: Q5.1 (G), R7.1, R9.2
unnamed: R2.1, U10.23 (IREF)
unnamed: R5.1, U12.4 (VREF)
unnamed: R14.1, U3.1 (EN)
unnamed: R5.2, R15.1, U12.5 (FB)
unnamed: R17.2, U8.8 (NO)
unnamed: R18.2, U8.2 (NC)
PD_MUX_OUT: C6.2, J13.1, J24.1, J25.1, R13.1, U4.4 (IN-), U19.1 (COMMONINPUT/OUTPUT), U20.1 (COMMONINPUT/OUTPUT)
PD_REF_PWM: J21.5, JP8.1 (A), U1.13 (RCLK/SDO), U7.2
S_PD_OUT1: D9A1.1 (K), U19.2 (I7)
S_PD_OUT2: D9B1.1 (K), U19.3 (I6)
S_PD_OUT3: D10A1.1 (K), U19.4 (I5)
S_PD_OUT4: D10B1.1 (K), U19.5 (I4)
S_PD_OUT5: D11A1.1 (K), U19.6 (I3)
S_PD_OUT6: D11B1.1 (K), U19.7 (I2)
S_PD_OUT7: D12A1.1 (K), U19.8 (I1)
S_PD_OUT8: D12B1.1 (K), U19.9 (I0)
S_PD_OUT9: D13A1.1 (K), U19.16 (I15)
S_PD_OUT10: D13B1.1 (K), U19.17 (I14)
S_PD_OUT11: D14A1.1 (K), U19.18 (I13)
S_PD_OUT12: D14B1.1 (K), U19.19 (I12)
S_PD_OUT13: D15A1.1 (K), U19.20 (I11)
S_PD_OUT14: D15B1.1 (K), U19.21 (I10)
S_PD_OUT15: D16A1.1 (K), U19.22 (I9)
S_PD_OUT16: D16B1.1 (K), U19.23 (I8)
THERM_AIR: TAIR1.1, U9.8 (I1)
THERM_EXT1: TEXT1.1, U9.6 (I3)
THERM_EXT2: TEXT2.1, U9.5 (I4)
THERM_EXT3: TEXT3.1, U9.4 (I5)
THERM_EXT4: J28.1, U9.23 (I8)
THERM_EXT5: J28.2, U9.22 (I9)
THERM_EXT6: J28.3, U9.21 (I10)
THERM_EXT7: J28.4, U9.20 (I11)
THERM_EXT8: J28.5, U9.19 (I12)
THERM_EXT9: J28.6, U9.18 (I13)
THERM_EXT10: J28.7, U9.17 (I14)
THERM_EXT11: J28.8, U9.16 (I15)
THERM_LID: TLID1.1, U9.7 (I2)
THERM_MUX_OUT: U2.10 (AIN1), U8.1 (COM), U9.1 (COMMONINPUT/OUTPUT)
THERM_WELL: TWELL1.1, U9.9 (I0)
VIN_SENSE: R19.2, R20.1

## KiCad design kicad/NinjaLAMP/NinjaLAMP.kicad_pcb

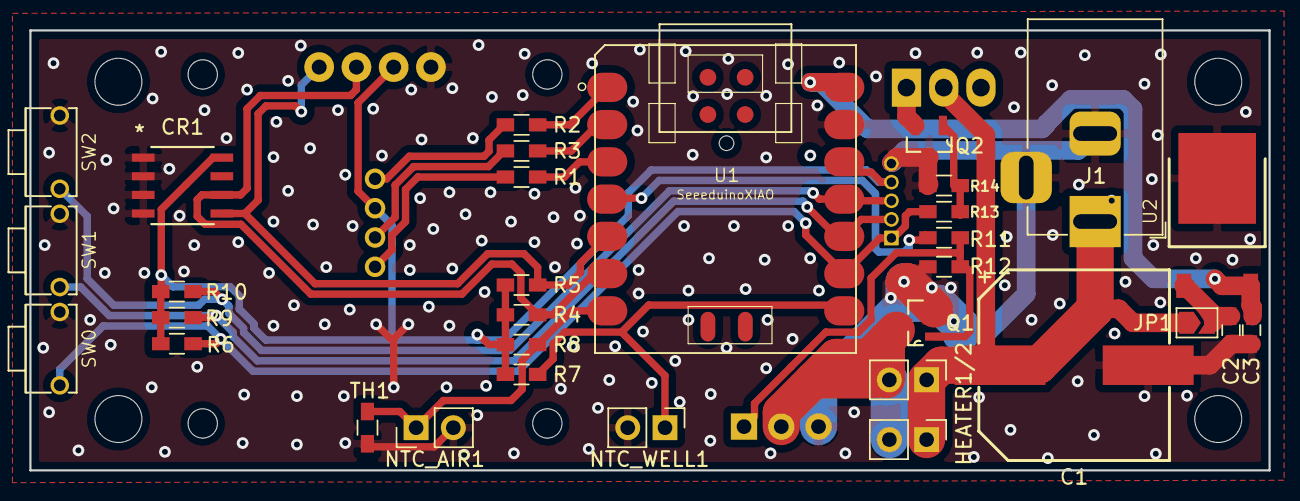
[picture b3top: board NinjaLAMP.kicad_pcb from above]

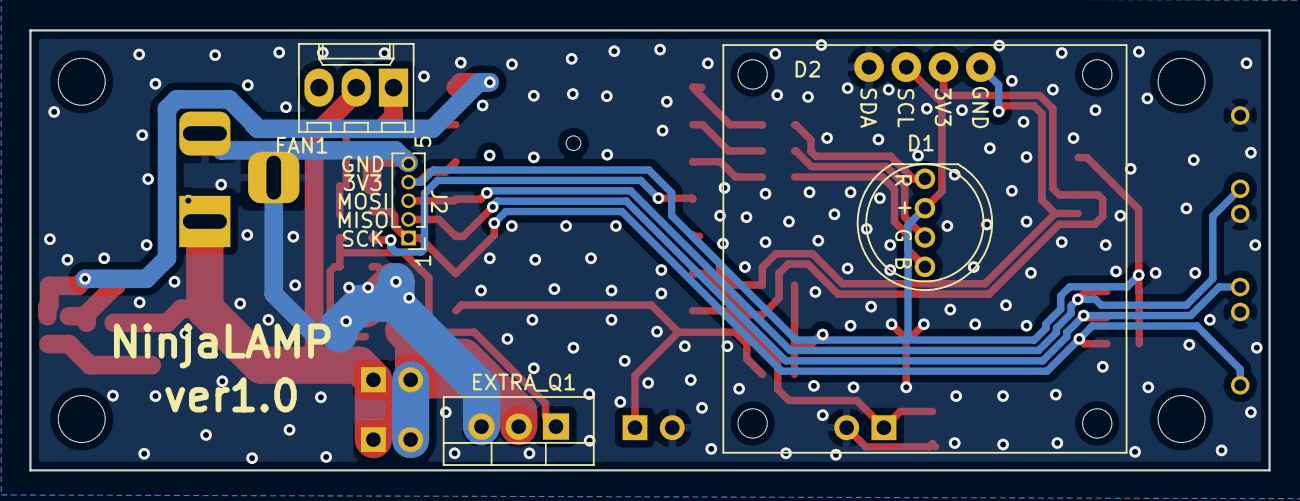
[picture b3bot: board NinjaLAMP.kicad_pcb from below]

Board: 2 copper layers, 84.5 x 30.0 mm, 37 parts (5 on the bottom side), 23 nets.

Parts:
C1: CP; ELECTRO-SMD-C-12.5x13.5MM
C2: 0.33uF; C_0603_HandSoldering
C3: 0.1uF; C_0603_HandSoldering
CR1: M24C02-RMN6TP
D1: DIP-LED-RGB-COMMON-ANODE_4P-D8MM_; LED4-2.0-D8.0MM
D2: I2C_SSD1306_LCD
EXTRA_Q1: BSP89; TO-220-3_Vertical
FAN1: Fan_3pin; Molex_KK-6410-03_03x2.54mm_Straight
HEATER1, HEATER2: Conn_01x02_Female; Pin_Header_Straight_1x02_Pitch2.54mm
J1: Barrel_Jack_Switch; BarrelJack_Horizontal
J2: Conn_01x05_Male; Pin_Header_Straight_1x05_Pitch1.27mm
JP1: Jumper; SolderJumper-2_P1.3mm_Open_TrianglePad1.0x1.5mm
NTC_AIR1: Conn_01x02_Female; Pin_Header_Straight_1x02_Pitch2.54mm
NTC_WELL1: Conn_01x02_Female; Pin_Header_Straight_1x02_Pitch2.54mm
Q1, Q2: BSP89; SOT95P240X112-3N
R1, R3: 15; R_0603_HandSoldering
R2: 75; R_0603_HandSoldering
R4, R5, R6, R7, R8, R9, R10, R12, R14: 47K; R_0603_HandSoldering
R11, R13: 1K; R_0603_HandSoldering
SW0, SW1, SW2: DIP-BUTTON_2P-6.0X3.0X4.3MM_; SW2-5.0-6.0X3.0X4.3MM
TH1: Thermistor; R_0603_HandSoldering
U1: SeeeduinoXIAO; SeeeduinoXIAO-MOUDLE14P-2.54-21X17.8MM
U2: PMIC-CJ78M05_TO-252_; TO-252

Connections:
+3V3: CR1.8, D1.3, D2.2, J2.4, R4.2, R5.2, R6.1, R7.1, R8.1, R9.1, R10.1, U1.12
+5V: C3.1, U1.14, U2.3
+12V: C1.1, FAN1.2, HEATER1.1, HEATER2.1, J1.1, JP1.1
/Q1: EXTRA_Q1.1, Q1.1, R11.1, R12.2
/Q2: EXTRA_Q1.2, HEATER1.2, HEATER2.2, Q1.3
AIN_AIR: NTC_AIR1.1, R8.2, TH1.1, U1.7
AIN_WELL: NTC_WELL1.1, R7.2, U1.8
GND: C1.2, C2.2, C3.2, CR1.1, CR1.2, CR1.3, CR1.4, D2.1, EXTRA_Q1.3, J1.2, J1.3, J2.5, NTC_AIR1.2, NTC_WELL1.2, Q1.2, Q2.3, R12.1, R14.1, SW0.2, SW1.2, SW2.2, TH1.2, U1.13, U2.2
HEATER: R11.2, U1.4
LED_B: R1.1, U1.3
LED_G: R3.1, U1.2
LED_R: R2.1, U1.1
unnamed: C2.1, JP1.2, U2.1
unnamed: D1.1, R1.2
unnamed: D1.2, R3.2
unnamed: D1.4, R2.2
unnamed: FAN1.1, Q2.2
unnamed: Q2.1, R13.1, R14.2
SCL: CR1.6, D2.3, R4.1, U1.6
SDA: CR1.5, D2.4, R5.1, U1.5
TACT0: J2.1, R6.2, R13.2, SW0.1, U1.9
TACT1: J2.2, R9.2, SW1.1, U1.10
TACT2: J2.3, R10.2, SW2.1, U1.11

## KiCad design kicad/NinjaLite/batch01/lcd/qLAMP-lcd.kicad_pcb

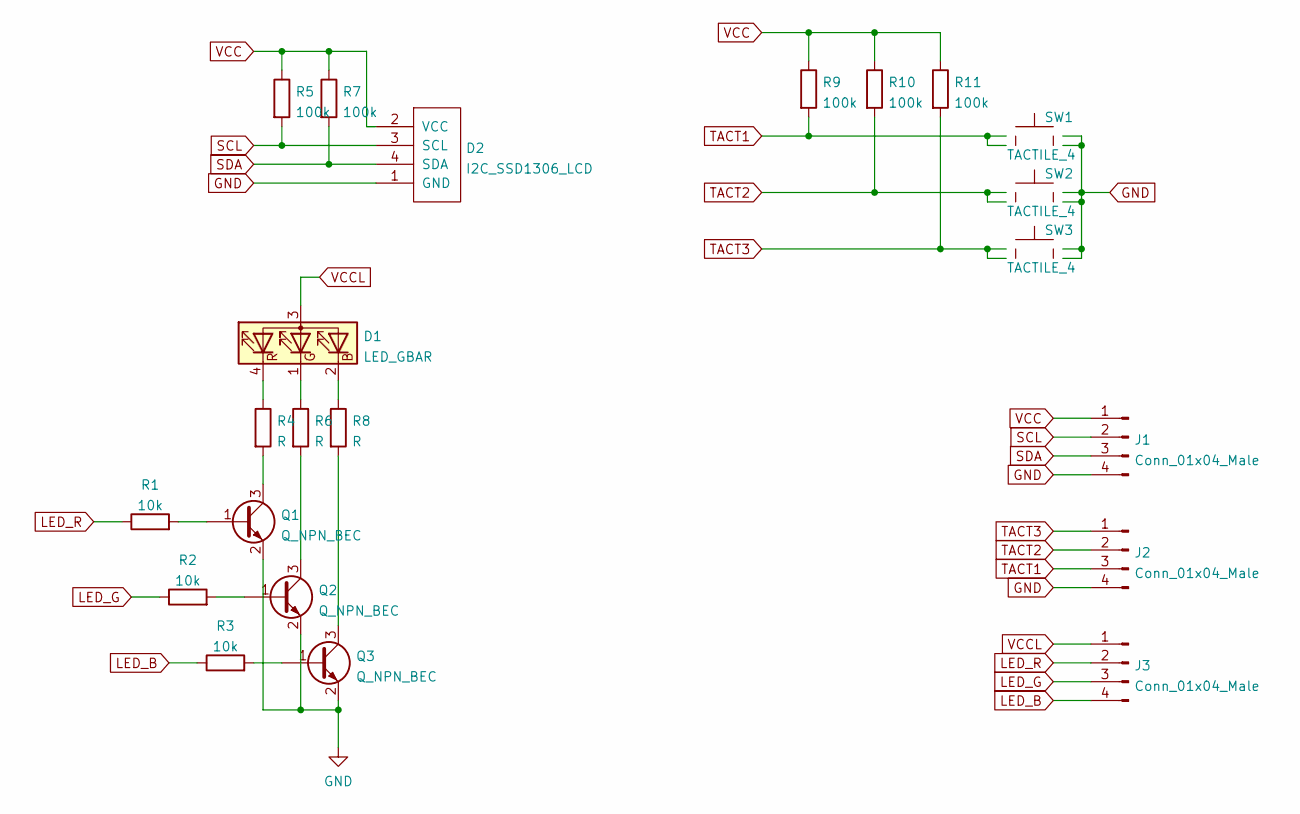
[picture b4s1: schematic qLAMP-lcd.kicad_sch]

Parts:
D1: LED_GBAR; LED_D5.0mm-4_RGB
D2: I2C_SSD1306_LCD
J1, J2, J3: Conn_01x04_Male; PinHeader_1x04_P2.54mm_Vertical
Q1, Q2, Q3: Q_NPN_BEC; SOT-23
R1, R2, R3: 10k; R_0603_1608Metric
R4, R6, R8: R; R_0603_1608Metric
R5, R7, R9, R10, R11: 100k; R_0603_1608Metric
SW1, SW2, SW3: TACTILE_4; SW_TH_Tactile_Omron_B3F-10xx

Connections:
GND: D2.1 (GND), J1.4, J2.4, Q1.2 (E), Q2.2 (E), Q3.2 (E), SW1.3, SW1.4, SW2.3, SW2.4, SW3.3, SW3.4
LED_B: J3.4, R3.1
LED_G: J3.3, R2.1
LED_R: J3.2, R1.1
unnamed: D1.1 (GK), R6.1
unnamed: D1.2 (BK), R8.1
unnamed: D1.4 (RK), R4.1
unnamed: Q1.1 (B), R1.2
unnamed: Q1.3 (C), R4.2
unnamed: Q2.1 (B), R2.2
unnamed: Q2.3 (C), R6.2
unnamed: Q3.1 (B), R3.2
unnamed: Q3.3 (C), R8.2
SCL: D2.3 (SCL), J1.2, R5.2
SDA: D2.4 (SDA), J1.3, R7.2
TACT1: J2.3, R9.2, SW1.1, SW1.2
TACT2: J2.2, R10.2, SW2.1, SW2.2
TACT3: J2.1, R11.2, SW3.1, SW3.2
VCC: D2.2 (VCC), J1.1, R5.1, R7.1, R9.1, R10.1, R11.1
VCCL: D1.3 (A), J3.1

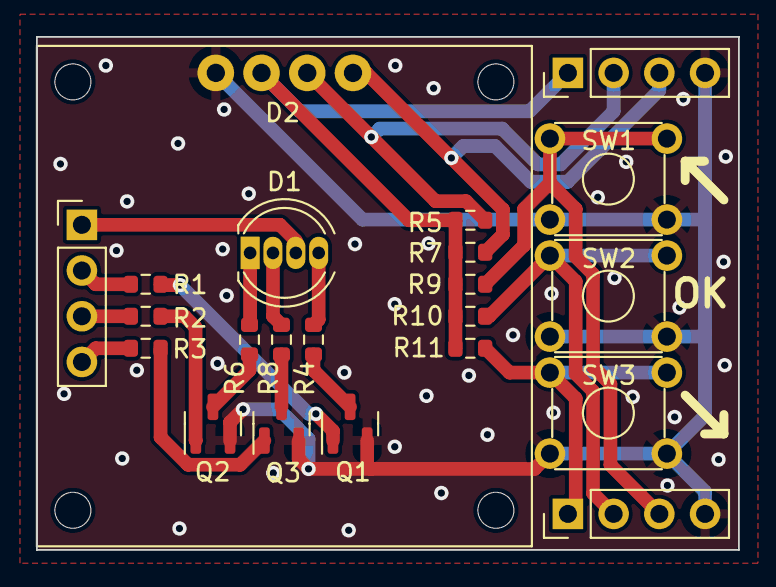
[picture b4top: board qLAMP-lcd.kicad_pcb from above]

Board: 2 copper layers, 39.0 x 28.5 mm, 22 parts (0 on the bottom side), 20 nets.

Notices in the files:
parts and their libraries:
Copyright 2021 Accelerated Designs. All rights reserved.
Copyright 2016 Accelerated Designs. All rights reserved.
